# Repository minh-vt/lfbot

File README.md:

# LF-Bot

Du an robot tu hanh bam line va vuot chuong ngai vat cho cuoc thi F-Maze-Solving tai Dai hoc FPT. Repository gom firmware ESP32 (`firmware/`), PCB base 1 mat lam tai nha (`hardware/`) va tai lieu (`docs/`).

## Bat dau

Cai `just` va cac cong cu build theo [huong dan phat trien](AGENTS.md), sau do xem cac tac vu tai thu muc goc:

```sh
just --list
```

Cac lenh thuong dung: `just test` de kiem thu, `just build` de dich firmware ESP32. Danh sach tac vu duoc quan ly trong [justfile](justfile).

## Tai lieu

- [Kien truc](docs/ARCHITECTURE.md), [trang thai](docs/IMPLEMENTATION.md) va [viec con lai](docs/PLAN.md)
- [Quyet dinh kien truc](docs/decisions/README.md)
- [Quy tac dong gop va lam viec voi agent](AGENTS.md)
- [The le](docs/manual.md) va [hoi dap cuoc thi](docs/fqa.csv)
- [BOM phan cung](docs/HARDWARE_BOM.csv)
- [Phan cung module va huong dan dau day](hardware/README.md)

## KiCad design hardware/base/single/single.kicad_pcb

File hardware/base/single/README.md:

# BASE 1 mặt: làm tại nhà với cầu nối 0 Ω

Cùng linh kiện với [PCB base](../README.md) bản 0.7; mạch điện giống, trừ hai chân ESP32 đổi chỗ và J10 không có +5V (xem [Thiết kế lại cho 1 mặt](#thiết-kế-lại-cho-1-mặt)). Toàn bộ đường mạch nằm ở **mặt dưới**. Chỗ phải bắc qua đường khác thì dùng **điện trở 0 Ω dán ở mặt dưới** hoặc **dây nhảy ở mặt trên**. Chỉ ăn mòn một mặt, không phải căn hai phim, không có mối hàn nào ở mặt trên. Đây là board xe dùng để thi.

**Trạng thái: bản 0.7, file làm mạch đã xuất, chưa làm thử.**
- **DRC** theo luật làm tay trong [single.kicad_pro](single.kicad_pro) (dây 0,3 mm, khe hở 0,25 mm): 0 lỗi, 0 cảnh báo, 0 chân hở, khớp schematic.
- **[check_top.py](gen/check_top.py):** 0 mối hàn mặt trên.
- **`check_weird.py` của KiCadRoutingTools:** không có đầu dây treo, mối nối mỏng, đồng trùng hay via nổi. Còn 2 đoạn đồng thừa ngắn (0,2 và 0,4 mm) nằm trong đồng cùng net (vô hại).
- **Firmware:** `firmware/esp32/pins.hpp` theo board này (SDA = GPIO15, TOF_XSHUT = GPIO17).
- **Lưu ý khi tự kiểm:** `board_score.py` và `route_review.py` của KiCadRoutingTools báo nhiều net "hở" trên board này. Chúng không hiểu footprint cầu nối (hai pad cùng số, KiCad coi là nối với nhau). Đã kiểm: tắt cờ cầu nối thì KiCad cũng báo đúng các chỗ đó, bật lại thì 0. Với board này, DRC của KiCad là chuẩn.

## So với bản 2 lớp (`../fab`)

| | Bản 2 lớp | **1 mặt (bản này)** |
|---|---|---|
| Ăn mòn | xưởng làm, mạ lỗ | **1 mặt, tại nhà** |
| Qua đường khác | 36 via mạ lỗ | **3 điện trở 0 Ω + 2 dây nhảy** |
| Lỗ khoan | — | **153** |
| Mối hàn ở mặt trên | — | **0** |
| GND | đổ hai mặt | đổ mặt dưới |

Khác so với bản xưởng:
- D1 (SS14) nằm ở mặt dưới, dưới module buck: mặt dưới chỗ đó trống, module chỉ có chân xuyên qua. D1 thẳng hàng với chân 5V của ESP32 (U1.21) nên +5V là một đường thẳng; anode chéo 45° tới chân OUT+ của buck. VBAT_SW chạy dưới thân D1, giữa hai pad, nên không cần cầu nối ở đó.
- Chia áp đo pin xếp lại quanh chân ADC (U1.41): đầu VBAT_SENSE của R1 và R2 quay vào nhau hai bên chân đó, C2 (song song R2) nằm ngay trên R2, chân đối chân. VBAT_SENSE còn khoảng 9 mm đồng (trước 15 mm).
- J4 (chọn chân IR của thanh) dời lên dải trước, cạnh J3. J10 (I2C mở rộng) dời vào giữa mép phải, ngay trên bus.
- SDA và TOF_XSHUT đổi chân ESP32; J10 chân 1 để trống.

## Cầu nối

- **3 điện trở 0 Ω** dán ở mặt dưới, tên JP… trên `so_do_lap_mat_duoi.pdf`:
  - JP1 (1206): VBAT_SW qua MOT_L_A, gần DRV trái;
  - JP2 (0805): ENC_L_B qua ENC_L_A, gần giắc encoder trái;
  - JP3 (1206): GND qua +3V3, cạnh U1.1, nối mảnh GND quanh chân AD0 của IMU (J6.7).
  - Mua dư: vài cái 0805 và 1206.
- **2 dây nhảy ở mặt trên** (4 lỗ), tổng khoảng 11,5 mm, dài nhất 6,4 mm:
  - +3V3 qua ba đường bus, ngay dưới J10;
  - IMU_INT qua ba đường bus, dưới module ESP32.
  Dây đồng có vỏ bọc (hoặc dây trần nếu ngắn và không chạm gì), xỏ qua hai lỗ riêng, hàn ở mặt dưới.
- **2 lỗ dây nhảy IMU_INT nằm dưới bi cầu**, ở (4,5; −51,5) và (7,3; −55,4): giũa mối hàn mặt dưới cho phẳng.

## File để làm ([release/v0.7](release/v0.7/))

Mọi trang 1:1 có **vạch 100 mm**. In xong đo vạch bằng thước: lệch là máy in đã co giãn.

| File | Dùng làm gì |
|---|---|
| `phim/dong_mat_duoi.pdf` | Phim mặt dưới, đồng màu đen. Không lật gương: úp mặt in vào đồng |
| `phim/dong_mat_duoi_AM-BAN.pdf` | Cùng phim, dạng âm bản (đồng trong suốt) |
| `phim/chu_mat_tren_ui_lat_guong.pdf` | Chữ in mặt trên để ủi (tuỳ chọn) |
| `phim/*_4ban.pdf` | Ba phim trên, mỗi tờ A4 dọc 4 bản (2 × 2, khe 6 mm để cắt rời): in thử, chọn bản đẹp nhất hoặc giữ làm dự phòng. Có thêm vạch 100 mm dọc bên cạnh: đo cả hai chiều, vì máy in có thể co giãn mỗi chiều một khác |
| `so_do_day_nhay_mat_tren.pdf` | Vị trí 2 dây nhảy, nhìn từ trên. **Không phải phim** |
| `so_do_lap_mat_tren.pdf`, `so_do_lap_mat_duoi.pdf` | Sơ đồ lắp; mặt dưới vẽ như nhìn từ dưới lên, có các điện trở 0 Ω. In 1:1 rồi đặt devkit, DRV, gá motor, thanh IR, bi cầu, buck lên giấy để kiểm lỗ trước khi làm mạch |
| `khoan/single-PTH.drl`, `single-NPTH.drl`, `*-drl_map.pdf` | File khoan và bản đồ lỗ |
| `LF-Bot_base-1side_v0.7_gerber.zip` | Gửi xưởng (in mạch 1 lớp hoặc phay CNC). Trong zip có `GHI_CHU_DAT_XUONG.txt`: 1 lớp đồng ở **mặt dưới**, mọi lỗ không mạ, kích thước, khe oval, luật nhỏ nhất. Đặt hàng chọn 1 lớp, FR-4 1,6 mm, và chép ý chính của ghi chú vào ô ghi chú đơn hàng |
| `LF-Bot_base-1side_v0.7.step` | Mô hình 3D để ghép trong CAD cơ khí |

**Chọn phim theo loại keo** như bản 2 mặt: phim khô hoặc keo UV loại âm dùng `AM-BAN`; tấm phủ sẵn cảm quang dương hoặc ủi mực laser dùng bản thường.

## Các bước

1. **Mặt trên không giữ đồng:** dùng phíp 1 mặt, hoặc với phíp 2 mặt thì không phủ keo mặt trên để FeCl₃ ăn hết đồng mặt đó. Nếu còn sót đồng ở mặt trên, mọi chân linh kiện xuyên lỗ sẽ chập vào nhau.
2. **Tạo mạch mặt dưới:** in phim, phủ keo, chiếu UV, rửa hiện hình, ăn mòn, tẩy keo.
3. **Ủi chữ mặt trên** (tuỳ chọn).
4. **Khoan** theo chấm tâm (153 lỗ):

   | Mũi | Lỗ | Số lỗ |
   |---|---|---|
   | 0,7 mm | lỗ dây nhảy (4); chân giắc JST ZH 0,73 mm (12) | 16 |
   | 0,8 mm | chân C1 | 2 |
   | 1,0 mm | header, socket, IMU (93); chân F1 (2) | 95 |
   | 1,2 mm | nút (8); pad dây công tắc (2); pad dây DRV (8) | 18 |
   | 1,3 mm | chân buck | 8 |
   | 1,8 mm | pad dây pin | 2 |
   | 2,2 mm | lỗ gá motor (4); 2 khe bi cầu | 4 + 2 khe |
   | 3,2 mm | lỗ khay pin (4); 2 khe thanh IR | 4 + 2 khe |
5. **Linh kiện dán ở mặt dưới:**
   - 18 điện trở và tụ;
   - D1 dưới chỗ module buck, vạch quay về phía ESP32 (+5V). Hàn trước khi lắp buck; đường VBAT_SW chạy giữa hai pad (khe 0,45 mm mỗi bên), không để thiếc tràn;
   - 3 điện trở 0 Ω, đặt theo tên JP trên sơ đồ lắp mặt dưới.
   - 16 điện trở chia áp IR nằm thành 8 cột sau J3, 10k ở hàng gần J3, 47k ở hàng sau. Nhìn từ mặt dưới, cột D1 ở bên phải.
6. **2 dây nhảy ở mặt trên** theo `so_do_day_nhay_mat_tren.pdf`, hàn ở mặt dưới. Làm trước các linh kiện cao để dễ luồn dây.
7. **Linh kiện xuyên lỗ:** tất cả hàn ở mặt dưới như mạch 1 mặt bình thường, kể cả C1 (lắp sát board được).
8. **Kiểm trước khi cắm module:**
   - đo thông GND giữa J1, pad GND của U2/U3 và chân GND của ESP32;
   - đo thông hai đầu mỗi dây nhảy và mỗi điện trở 0 Ω;
   - đo không chập VBAT_SW–GND, +5V–GND, +3V3–GND;
   - cấp nguồn khi chưa cắm ESP32, chỉnh buck lên khoảng 5,2–5,3 V.

Cách đấu module: [wiring.md](../../wiring.md). Danh sách mua linh kiện chung: [../fab/release/v0.7](../fab/release/v0.7/README.md); thêm các điện trở 0 Ω ở trên.

## Sinh lại

Đọc vị trí từ `../fab/base.kicad_pcb`:

- [gen/make_single.sh](gen/make_single.sh), khoảng 3 phút:
  - gỡ đồng;
  - [gen/prepare.py](gen/prepare.py): chuyển linh kiện dán và D1 xuống dưới, dời J4, J10 và D1, gán net theo `VARIANT_PINS` trong `../gen/design.py`, đánh dấu các chân nối sẵn bên trong linh kiện, cấm đồng mặt trên ở mọi pad, cấm dây nhảy dưới thân linh kiện áp sát board;
  - [gen/guide.py](gen/guide.py): vẽ sẵn bus I2C/ToF và IR_CTRL, khoá lại;
  - đổ GND mặt dưới;
  - route phần còn lại bằng KiCadRoutingTools, mặt trên đắt gấp 30 lần để chỉ dùng khi mặt dưới hết đường. Thứ tự: nguồn, kênh IR, phần còn lại. GND không đưa vào lượt nào, vì bước tự nối GND của KiCadRoutingTools sẽ kéo đồng GND lên mặt trên;
  - làm gọn (`../gen/tidy_tracks.py`), đưa đầu dây vào tâm lỗ (`../gen/center_vias.py`);
  - [gen/jumpers.py](gen/jumpers.py), mỗi bước chỉ giữ khi DRC không báo lỗi mới: đổi dây nhảy ngắn thành 0 Ω 0805 hoặc 1206, trượt dọc dây cho đường bên dưới nằm giữa hai pad; gộp chuỗi "dây – đoạn dưới – dây" thành một dây; thay 0 Ω không bắc qua gì bằng đoạn đồng. Chạy cả hai thứ tự (0 Ω trước, gộp trước) rồi giữ bản ít lỗ hơn;
  - [gen/gnd_bridges.py](gen/gnd_bridges.py): mảnh GND nào bị đường mạch bao kín thì nối sang mảnh gần nhất bằng 0 Ω (hoặc dây nhảy nếu xa), giữ khi DRC cho phép;
  - [gen/prune.py](gen/prune.py): bỏ đồng không mang dòng: đoạn mà `check_weird` của KiCadRoutingTools coi là bỏ được, và đoạn nối thẳng hai chân đã nối sẵn trong linh kiện (router không biết các chân đó nối trong, KiCad thì biết). Mỗi đoạn chỉ bỏ khi DRC không báo lỗi hay chân hở mới;
  - sắp nhãn, chạy DRC.
- [gen/export.sh](gen/export.sh): xuất `release/<bản>`.
- Schematic `single.kicad_sch` do `../gen/run_all.sh` sinh cùng bản 2 lớp, với các chân đổi trong `VARIANT_PINS`. Footprint `Jumper_0R_0805` và `Jumper_0R_1206` do `../gen/gen_fp.py` sinh.

## Thiết kế lại cho 1 mặt

Bản trước (route tự động hoàn toàn) cần 24 cầu nối, 18 lỗ. Ba điều về hình học của board quyết định số đó:

- **Dải chia áp chỉ có một khe trống.** 8 cột điện trở có 9 khe, mỗi khe chỉ lọt một đường 0,3 mm. 8 đường ADC đã cần 8 khe, chỉ còn khe x = 1,27 mm (giữa cột IR4 và IR5, thẳng hàng với khe giữa chân 6 và 7 của J3).
- **GND của các điện trở 47k chỉ vào được từ phía module.** Mỗi pad GND kẹp giữa hai đường ADC, nối được qua khe giữa các chân hàng trước của ESP32. Dải ngay sau hàng chân đó phải để cho GND.
- **Thứ tự chân của ToF (SDA, SCL, XSHUT), IMU và J10 cố định.**

Thiết kế lại theo đó:

- **Đổi SDA và TOF_XSHUT trên ESP32** (SDA sang U1.8 = GPIO15, XSHUT sang U1.10 = GPIO17). Ba đường bus khi chui xuống dưới module thì nằm cạnh nhau đúng thứ tự ToF cần.
- **Bus đi vòng, không bắt chéo gì:** từ U1.8–U1.10 xuống dưới module, chạy dưới thân IMU (cách dải GND sau hàng chân), rẽ lên mép phải, đi xuyên qua chân SDA/SCL của IMU (J6.4, J6.3) rồi của J10 (J10.4, J10.5; XSHUT đi khe bên cạnh), dọc mép trước rồi vào ToF đúng thứ tự chân. IMU giữ nguyên chỗ: chân SDA/SCL của nó vốn nằm đúng trên đường đi lên.
- **IR_CTRL lấy khe trống duy nhất** của dải chia áp để lên J4, nay đặt ở dải trước.
- **Bỏ +5V khỏi J10:** nhánh này trước đi vòng gần hết board.
- **Cầu nối miễn phí:** các chân mà linh kiện đã nối sẵn bên trong được khai báo là nối với nhau, nên đường mạch được dùng chúng để đi qua: hai chân cùng phía của mỗi nút 6 mm, các chân GND và hai chân 3V3 của DevKit ESP32, hai chân của mỗi cực MP1584 (cùng xuyên qua một pad của module), GND vào và ra của MP1584.
- **D1 dưới module buck**, thẳng hàng chân 5V của ESP32: +5V không còn vòng ra ngoài module rồi bắt chéo VBAT_SW.

Kết quả: 3 điện trở 0 Ω + 2 dây nhảy (4 lỗ). Mỗi cầu còn lại có lý do riêng: IMU_INT và +3V3 phải vượt ba đường bus để tới IMU và phía sau board; hai cầu ở phía sau (VBAT_SW qua motor trái, encoder trái) có từ bản đầu; JP3 nối mảnh GND quanh chân AD0 của IMU.

## Đã thử giảm cầu nối

Mục tiêu: ít cầu nối nhất mà vẫn nối đủ mọi net. Mỗi cách đều xây lại toàn bộ board rồi đếm:

| Cách | Kết quả |
|---|---|
| Cho đường mạch chạy dưới thân linh kiện có sẵn (D1, điện trở, tụ) thay cho cầu nối | KiCadRoutingTools vốn được phép làm vậy (bản xưởng có đường chạy dưới C2, R21, R22). Ở chỗ cũ của D1 nó không thấy lợi; khi D1 vào dưới module buck thì VBAT_SW chạy dưới thân D1 và bỏ được một dây nhảy |
| Thay điện trở 0 Ω không bắc qua gì bằng dây đồng thẳng | Bớt được 2 cái (17 → 15) |
| Trượt 0 Ω dọc dây nhảy: khe 0,8 mm của 0805 chỉ vừa một đường 0,3 mm với khe hở 0,25 mm mỗi bên, mà router không đặt đường vào giữa | Thêm được 0 Ω ở những chỗ trước bị chạm pad |
| Gộp chuỗi "dây – đoạn dưới – dây": router xuống mặt dưới một đoạn ngắn chỉ để một dây khác đi qua, nhưng dây có vỏ được bắt chéo nhau | 5 chuỗi gộp được. Cùng hai bước trên: 13 → 9 dây nhảy, 26 → 18 lỗ |
| Phạt via nặng hơn trong KiCadRoutingTools (`--via-cost` 1000–3000, mặt trên đắt gấp 100 lần) | Tệ hơn: các đường đi vòng xa chặn net route sau, còn 6–13 đường chưa nối, có dây dài 112 mm |
| Bỏ +5V khỏi J10 | Một lần route còn 4 đường chưa nối: router quá nhạy với thay đổi nhỏ để kết luận |
| Bỏ +5V khỏi J10 và vẽ tay trước bus mà không đổi chân: SCL qua khe giữa dải chia áp, SDA/SCL dưới module ESP32 sang IMU và J10, IR_CTRL dưới module sang J4 (8 cách phối hợp) | Bản tốt nhất có 23 cầu nối nhưng vẫn còn mảnh GND rời; nối các mảnh đó thì thành khoảng 25 |
| Thiết kế lại ở trên (đổi chân SDA/XSHUT, dời J4/J10, bus vẽ tay), D1 còn ở chỗ cũ cạnh buck | 6 cầu nối, 6 lỗ |
| Như trên, D1 dưới module buck | **5 cầu nối, 4 lỗ**: đang dùng |
| Vẽ tay thêm +3V3 (một dây nhảy phía bắc J10 xuống IMU) | 11 cầu nối: router đổi cách đưa +3V3 ra phía sau và bắt chéo encoder; không dùng |
| Hoán đổi chân GPIO bằng target swap của KiCadRoutingTools | Không bớt được cầu nối nào, lại đổi bảng chân; không dùng |
| Đặt lại J10, J4, J9, nút, D1, R1/R2/C2 bằng placer của KiCadRoutingTools (12 phương án, 6 phương án tốt nhất được route đầy đủ) | Các phương án ít cầu nối hơn đều còn 3–16 đường chưa nối, mà mỗi đường hở lại cần thêm cầu nối; không phương án nào hơn |

Router đặt từng net một, theo đường ngắn nhất lúc đó, nên không tìm cách sắp xếp ít chỗ bắt chéo cho cả board. Vì vậy bus được vẽ tay, router chỉ làm phần còn lại.

## Giới hạn

- Chưa làm thử.
- Không có lớp phủ xanh: hàn cẩn thận chỗ đường mạch chạy dưới điện trở 0 Ω (khe 0,25 mm).
- Pad giắc JST ZH chỉ có vành 0,15 mm, như hai bản kia.
- Mặt dưới còn 1 góc 90°, 2 đoạn lệch góc và 7 đoạn ngắn dưới 0,2 mm (đo bằng [geometry_report.py](../gen/geometry_report.py)), không ảnh hưởng điện. Chạy thêm `tidy_tracks.py` ở cuối không gọn hơn.

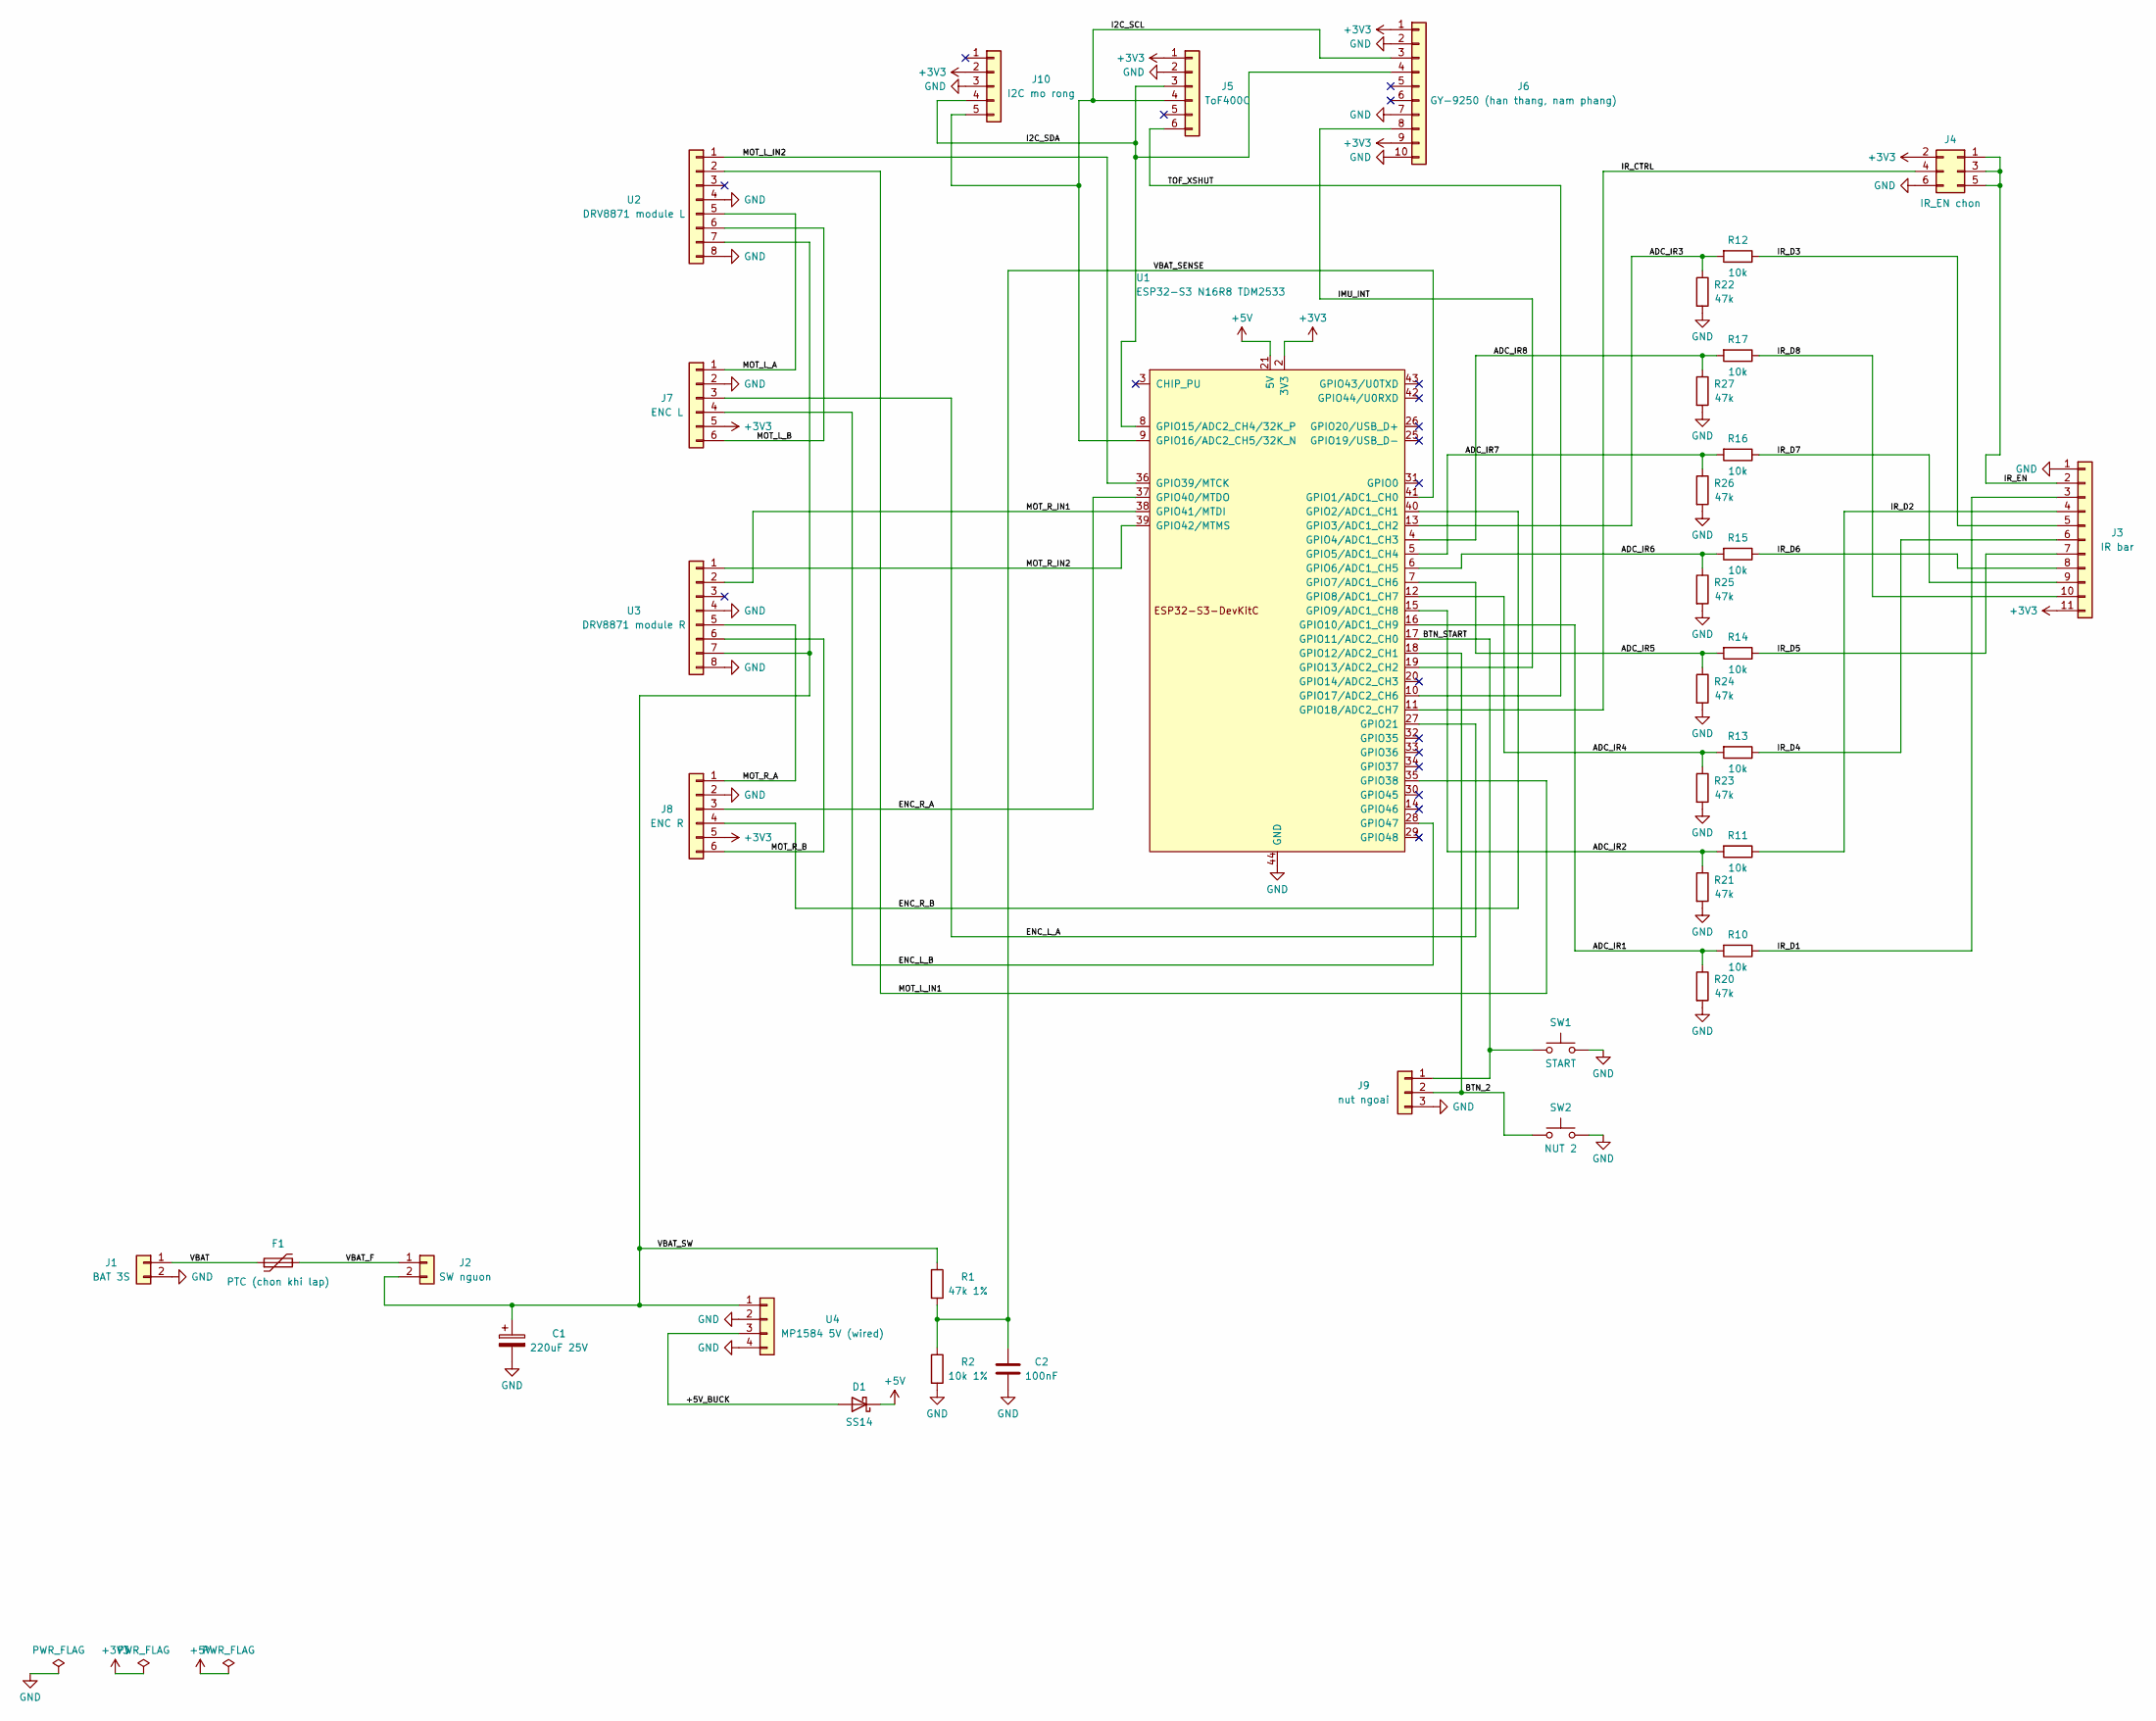
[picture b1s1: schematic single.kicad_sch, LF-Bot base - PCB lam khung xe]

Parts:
C1: 220uF 25V; CP_Radial_D6.3mm_P2.50mm
C2: 100nF; C_0805_2012Metric_Pad1.18x1.45mm_HandSolder
D1: SS14; D_SMA_Handsoldering
F1: PTC (chon khi lap); Fuse_Bourns_MF-RG500
J1: BAT 3S; SolderWire-1sqmm_1x02_P5.4mm_D1.4mm_OD2.7mm
J2: SW nguon; SolderWire-0.5sqmm_1x02_P4.8mm_D0.9mm_OD2.3mm
J3: IR bar; PinHeader_1x11_P2.54mm_Vertical
J4: IR_EN chon; PinHeader_2x03_P2.54mm_Vertical
J5: ToF400C; PinSocket_1x06_P2.54mm_Vertical
J6: GY-9250 (han thang, nam phang); GY9250_Flat
J7: ENC L; JST_ZH_B6B-ZR_1x06_P1.50mm_Vertical
J8: ENC R; JST_ZH_B6B-ZR_1x06_P1.50mm_Vertical
J9: nut ngoai; PinHeader_1x03_P2.54mm_Vertical
J10: I2C mo rong; PinHeader_1x05_P2.54mm_Vertical
R1: 47k 1%; R_0805_2012Metric_Pad1.20x1.40mm_HandSolder
R2: 10k 1%; R_0805_2012Metric_Pad1.20x1.40mm_HandSolder
R10, R11, R12, R13, R14, R15, R16, R17: 10k; R_0805_2012Metric_Pad1.20x1.40mm_HandSolder
R20, R21, R22, R23, R24, R25, R26, R27: 47k; R_0805_2012Metric_Pad1.20x1.40mm_HandSolder
SW1: START; SW_PUSH_6mm
SW2: NUT 2; SW_PUSH_6mm
U1: ESP32-S3 N16R8 TDM2533; ESP32-S3-DevKitC_TDM2533
U2: DRV8871 module L; DRV8871_Module
U3: DRV8871 module R; DRV8871_Module
U4: MP1584 5V (wired); MP1584_Wired

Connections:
+3V3: J3.11, J4.2, J5.1, J6.1, J6.9, J7.5, J8.5, J10.2, U1.1 (3V3), U1.2 (3V3)
+5V: D1.1 (K), U1.21 (5V)
/+5V_BUCK: D1.2 (A), U4.3
/ADC_IR1: R10.2, R20.1, U1.16 (GPIO10/ADC1_CH9)
/ADC_IR2: R11.2, R21.1, U1.15 (GPIO9/ADC1_CH8)
/ADC_IR3: R12.2, R22.1, U1.13 (GPIO3/ADC1_CH2)
/ADC_IR4: R13.2, R23.1, U1.12 (GPIO8/ADC1_CH7)
/ADC_IR5: R14.2, R24.1, U1.7 (GPIO7/ADC1_CH6)
/ADC_IR6: R15.2, R25.1, U1.6 (GPIO6/ADC1_CH5)
/ADC_IR7: R16.2, R26.1, U1.5 (GPIO5/ADC1_CH4)
/ADC_IR8: R17.2, R27.1, U1.4 (GPIO4/ADC1_CH3)
/BTN_2: J9.2, SW2.1, U1.18 (GPIO12/ADC2_CH1)
/BTN_START: J9.1, SW1.1, U1.17 (GPIO11/ADC2_CH0)
/ENC_L_A: J7.3, U1.27 (GPIO21)
/ENC_L_B: J7.4, U1.28 (GPIO47); also elsewhere on the board
/ENC_R_A: J8.3, U1.37 (GPIO40/MTDO)
/ENC_R_B: J8.4, U1.40 (GPIO2/ADC1_CH1)
/I2C_SCL: J5.4, J6.3, J10.5, U1.9 (GPIO16/ADC2_CH5/32K_N)
/I2C_SDA: J5.3, J6.4, J10.4, U1.8 (GPIO15/ADC2_CH4/32K_P)
/IMU_INT: J6.8, U1.19 (GPIO13/ADC2_CH2)
/IR_CTRL: J4.4, U1.11 (GPIO18/ADC2_CH7)
/IR_D1: J3.3, R10.1
/IR_D2: J3.4, R11.1
/IR_D3: J3.5, R12.1
/IR_D4: J3.6, R13.1
/IR_D5: J3.7, R14.1
/IR_D6: J3.8, R15.1
/IR_D7: J3.9, R16.1
/IR_D8: J3.10, R17.1
/IR_EN: J3.2, J4.1, J4.3, J4.5
/MOT_L_A: J7.1, U2.5
/MOT_L_B: J7.6, U2.6
/MOT_L_IN1: U1.35 (GPIO38), U2.2
/MOT_L_IN2: U1.36 (GPIO39/MTCK), U2.1
/MOT_R_A: J8.1, U3.5
/MOT_R_B: J8.6, U3.6
/MOT_R_IN1: U1.38 (GPIO41/MTDI), U3.2
/MOT_R_IN2: U1.39 (GPIO42/MTMS), U3.1
/TOF_XSHUT: J5.6, U1.10 (GPIO17/ADC2_CH6)
/VBAT: F1.1, J1.1
/VBAT_F: F1.2, J2.1
/VBAT_SENSE: C2.1, R1.2, R2.1, U1.41 (GPIO1/ADC1_CH0)
/VBAT_SW: C1.1, J2.2, R1.1, U2.7, U3.7, U4.1; also elsewhere on the board
GND: C1.2, C2.2, J1.2, J3.1, J4.6, J5.2, J6.2, J6.7, J6.10, J7.2, J8.2, J9.3, J10.3, R2.2, R20.2, R21.2, R22.2, R23.2, R24.2, R25.2, R26.2, R27.2, SW1.2, SW2.2, U1.22 (GND), U1.23 (GND), U1.24 (GND), U1.44 (GND), U2.4, U2.8, U3.4, U3.8, U4.2, U4.4; also elsewhere on the board

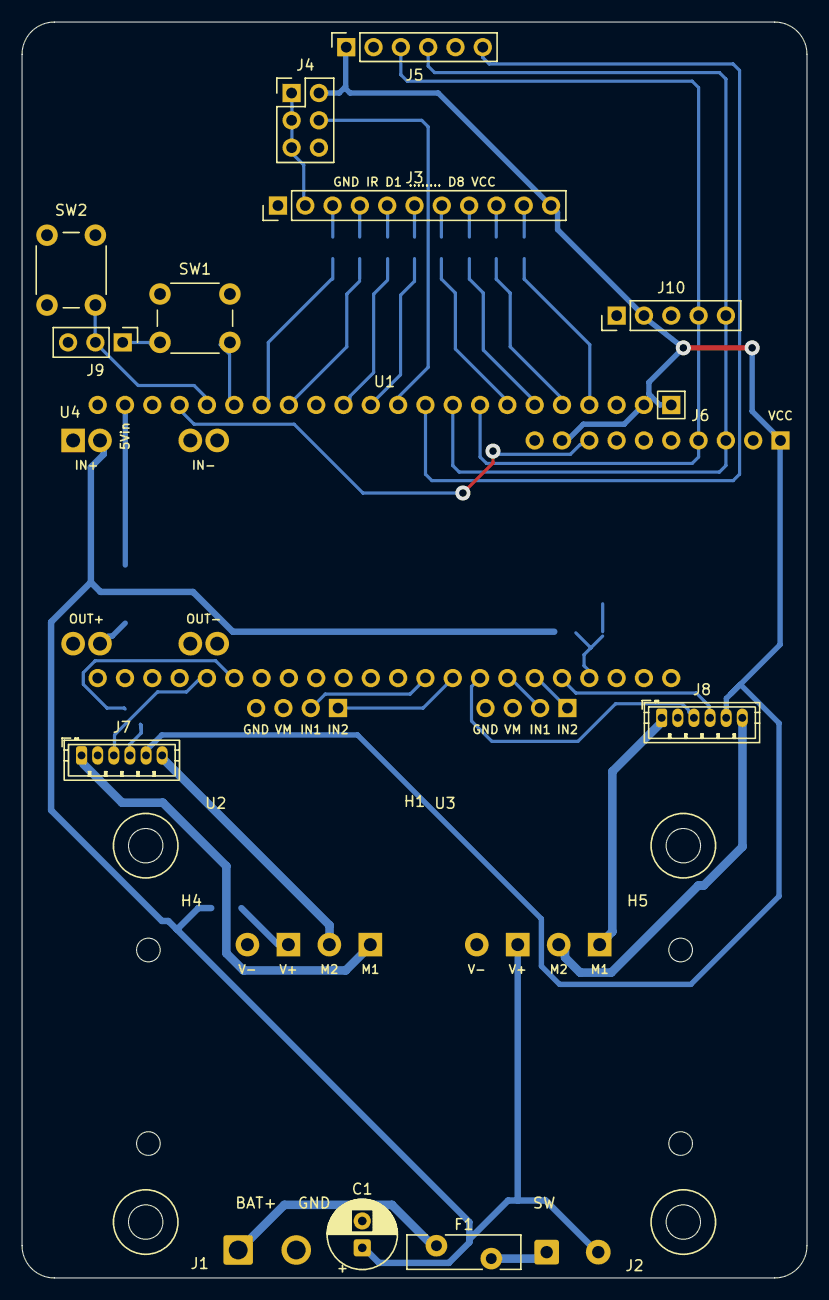
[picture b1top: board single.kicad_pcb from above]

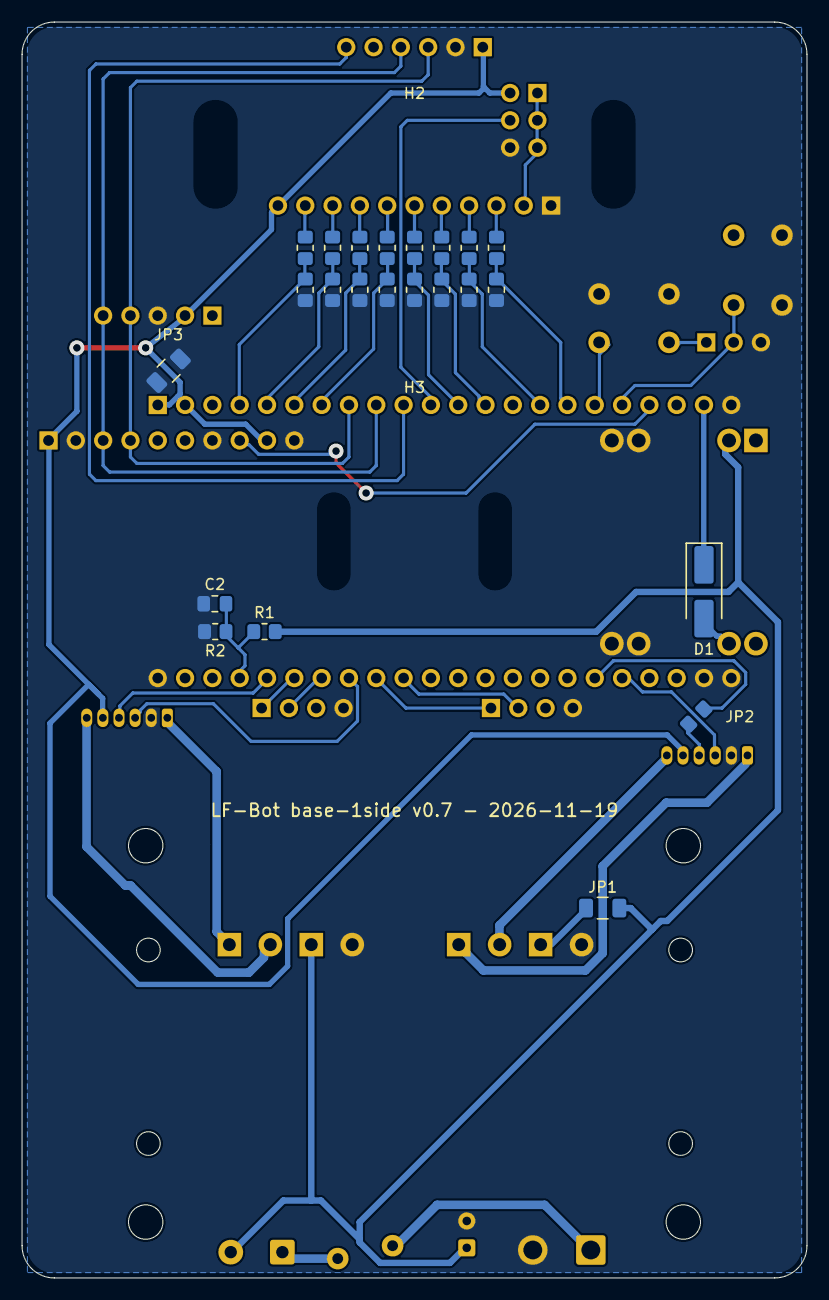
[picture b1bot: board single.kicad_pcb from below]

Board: 2 copper layers, 73.0 x 116.8 mm, 46 parts (25 on the bottom side), 44 nets.

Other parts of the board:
H1: Stack_Mount_50x35
H2: IR_Bar_Mount_37mm
H3: Caster_Mount_15mm
H4, H5: N20_Bracket_Mount
JP1, JP3: 0R 1206; Jumper_0R_1206
JP2: 0R 0805; Jumper_0R_0805

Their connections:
/ENC_L_B: JP2.1; also elsewhere on the board
/VBAT_SW: JP1.1; also elsewhere on the board
GND: JP3.1; also elsewhere on the board

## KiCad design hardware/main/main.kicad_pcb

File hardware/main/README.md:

# MAIN LF-Bot — đã dừng

> **Thiết kế PCB đã dừng theo [ADR-019](../../docs/decisions/ADR-019-module-based-hardware.md).** Dùng [pin map module](../wiring.md) và [BOM hiện hành](../../docs/HARDWARE_BOM.csv); không gia công, route tiếp hoặc đấu dây theo board này.

Board mang DevKit ESP32-S3 và hai IC A4950 cũ. Source KiCad vẫn mở được bằng KiCad 10 qua [main.kicad_pro](main.kicad_pro); [schematic](main.kicad_sch) và [PCB](main.kicad_pcb) là bản lưu lịch sử: hai mặt linh kiện, 14 SMD tín hiệu ở B.Cu, chưa route xong, chưa kiểm chứng Z/lắp ráp/nhiệt.

Tài liệu placement/routing/BOM của board đã được archive và bỏ khỏi cây làm việc. Lý do dừng PCB nằm ở [ADR-019](../../docs/decisions/ADR-019-module-based-hardware.md).

Giữ `Main.pretty/`, `Main.kicad_sym`, library table, [cơ khí](mechanical/) và [datasheet motor](datasheets/GA12-N20.pdf) để phục hồi. `Bracket.step` vẫn là nguồn gá motor được chủ dự án xác nhận. Không gửi Gerber cũ đi in.

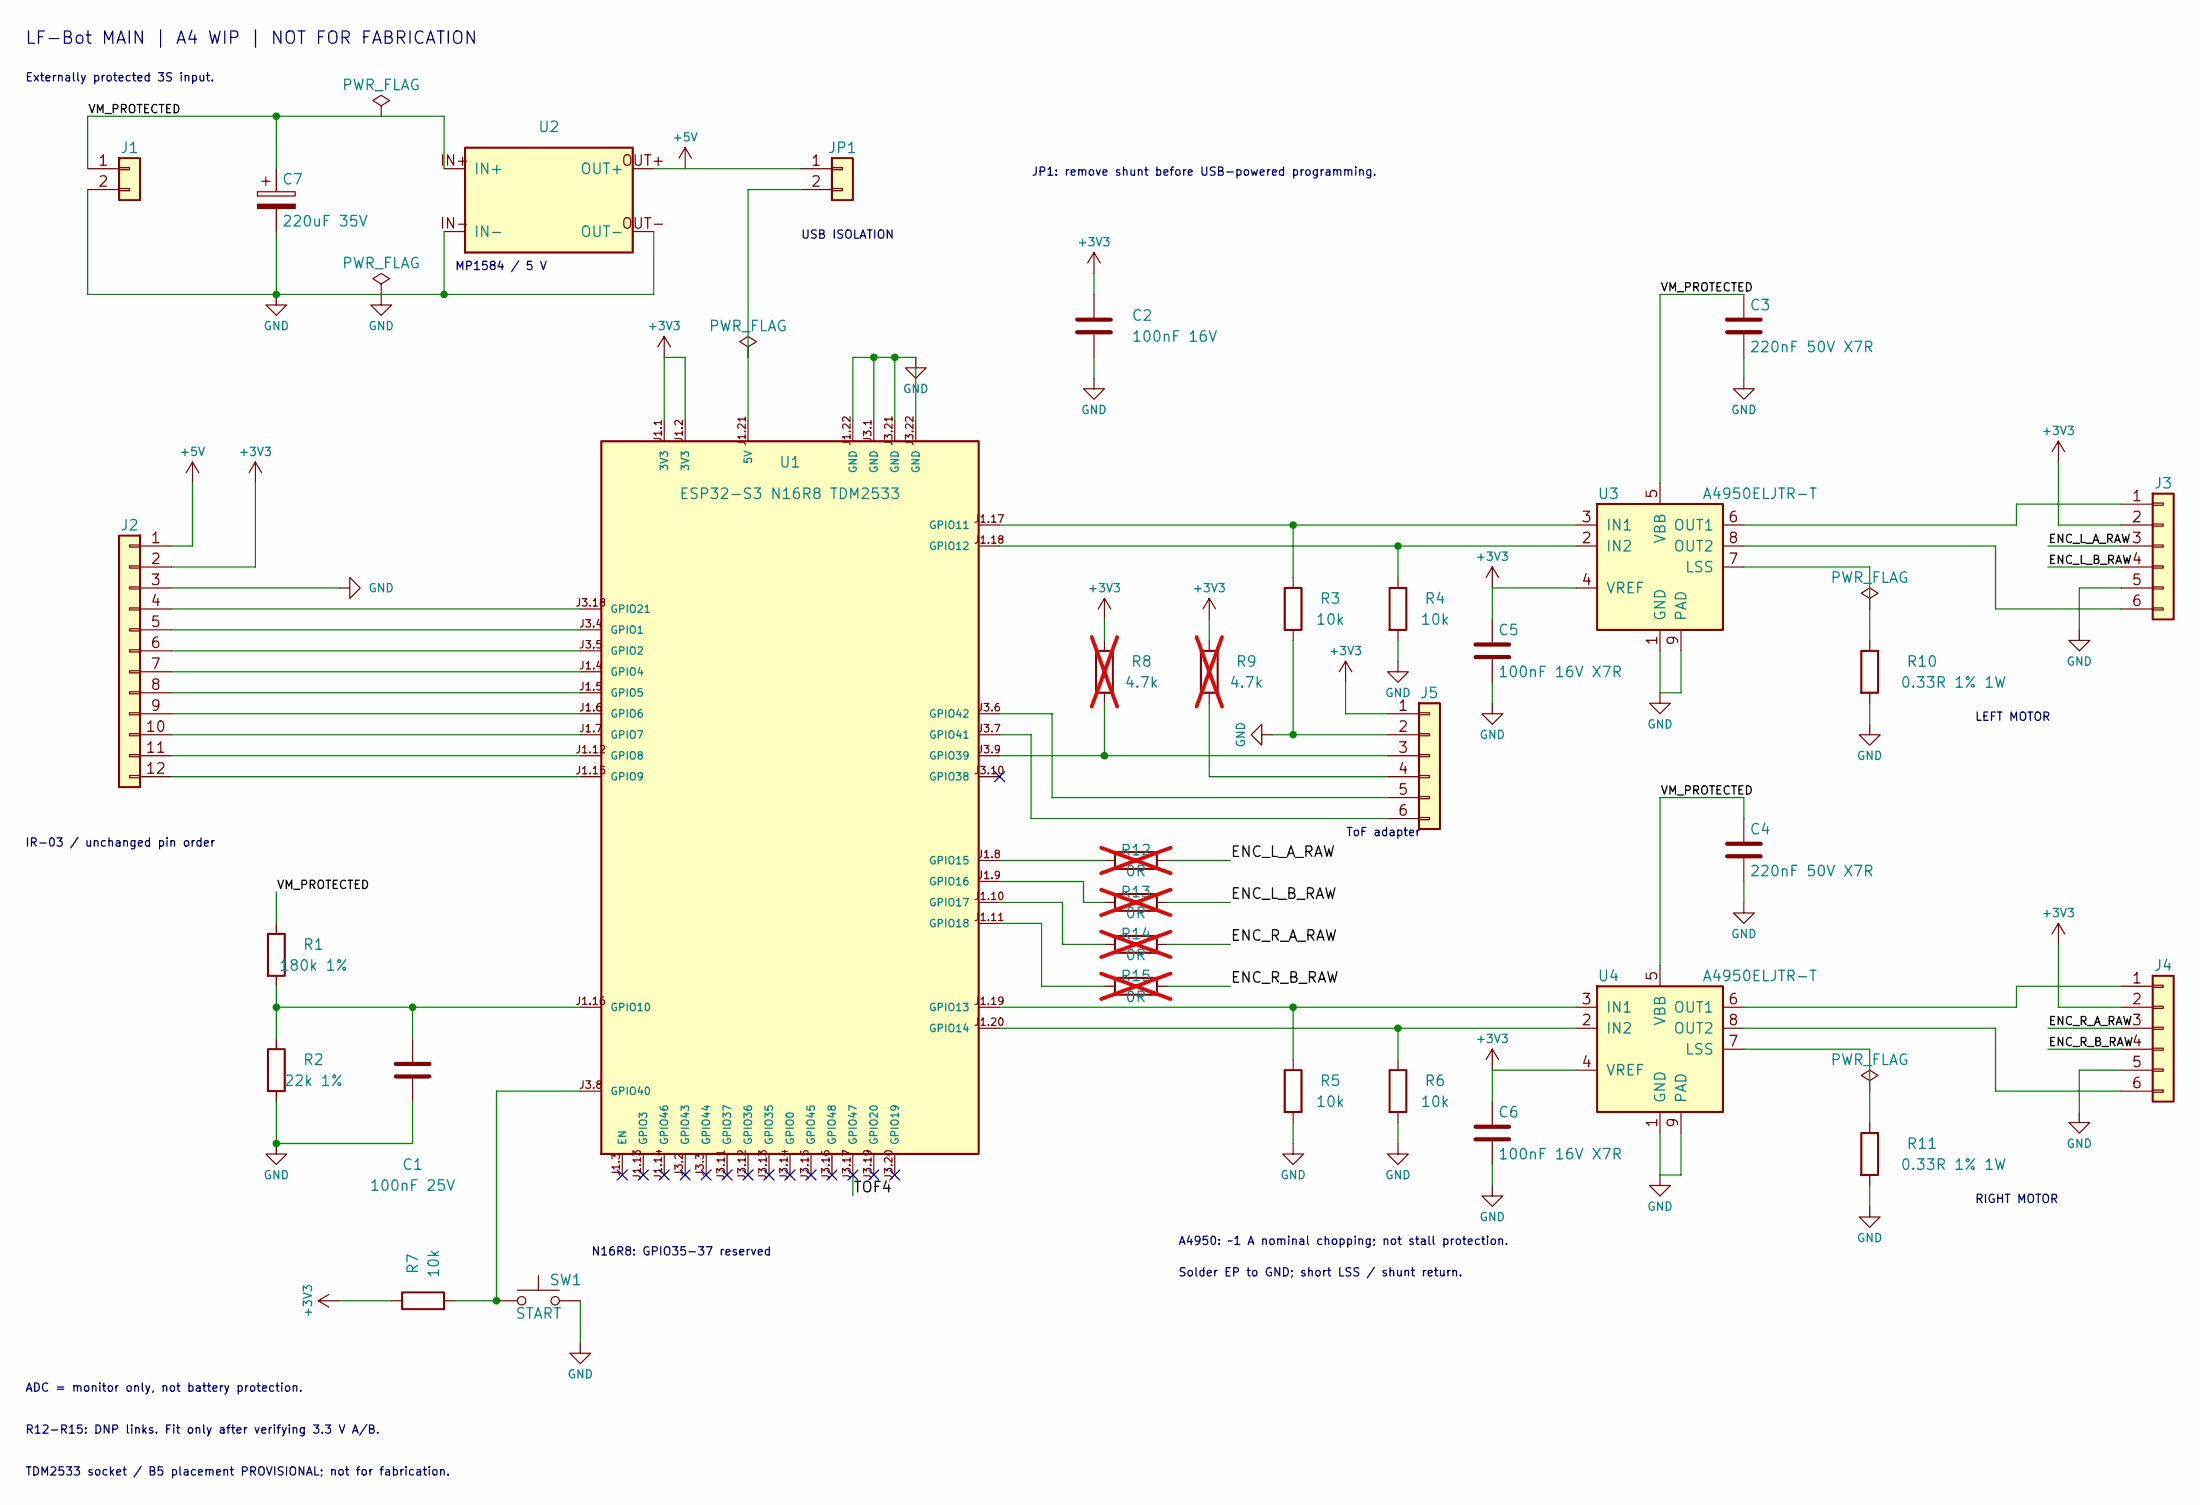
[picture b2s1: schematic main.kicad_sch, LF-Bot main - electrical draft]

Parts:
C1: 100nF 25V; C_0805_2012Metric
C2: 100nF 16V; C_0805_2012Metric
C3, C4: 220nF 50V X7R; C_0805_2012Metric
C5, C6: 100nF 16V X7R; C_0805_2012Metric
C7: 220uF 35V; CP_Radial_D8.0mm_P3.50mm; MPN 35ZLQ220MEFC8X11.5
J1: 3S PROTECTED INPUT / WIRED; SolderWire-0.5sqmm_1x02_P4.8mm_D0.9mm_OD2.3mm
J2: IR03 - SAME PINOUT AS IR BOARD; PinHeader_1x12_P2.54mm_Vertical
J3: LEFT MOTOR / XH 2.50; JST_XH_B6B-XH-A_1x06_P2.50mm_Vertical; MPN B6B-XH-A(LF)(SN)
J4: RIGHT MOTOR / XH 2.50; JST_XH_B6B-XH-A_1x06_P2.50mm_Vertical; MPN B6B-XH-A(LF)(SN)
J5: TOF400C / XH 2.50 ADAPTER; JST_XH_B6B-XH-A_1x06_P2.50mm_Vertical; MPN B6B-XH-A(LF)(SN)
JP1: REMOVE BEFORE USB POWER; PinHeader_1x02_P2.54mm_Vertical
R1: 180k 1%; R_0805_2012Metric
R2: 22k 1%; R_0805_2012Metric
R3, R4, R5, R6, R7: 10k; R_0805_2012Metric
R8, R9: 4.7k; R_0805_2012Metric; not fitted
R10, R11: 0.33R 1% 1W; R_2512_6332Metric
R12, R13, R14, R15: 0R; R_0805_2012Metric; MPN RC0805JR-070RL; not fitted
SW1: START; SW_PUSH_6mm_H5mm
U1: ESP32-S3 N16R8 TDM2533; ESP32-S3_DevKitC-1_Reference_Sockets; MPN TDM2533
U2: MP1584 FIXED 5V / WIRED; MP1584_Wire_Interface; MPN MP1584 fixed 5V module
U3, U4: A4950ELJTR-T; SOIC-8-1EP_3.9x4.9mm_P1.27mm_EP2.41x3.3mm; MPN A4950ELJTR-T

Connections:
+3V3: C2.1, C5.1, C6.1, J2.2, J3.2, J4.2, J5.1, R7.1, R8.1, R9.1, U1.J1.1 (3V3), U1.J1.2 (3V3), U3.4 (VREF), U4.4 (VREF)
+5V: J2.1, JP1.1, U2.OUT+
/ENC_L_A_RAW: J3.3, R12.2
/ENC_L_B_RAW: J3.4, R13.2
/ENC_R_A_RAW: J4.3, R14.2
/ENC_R_B_RAW: J4.4, R15.2
/TOF4: U1.J3.17 (GPIO47)
/VM_PROTECTED: C3.1, C4.1, C7.1, J1.1, R1.1, U2.IN+, U3.5 (VBB), U4.5 (VBB)
GND: C1.2, C2.2, C3.2, C4.2, C5.2, C6.2, C7.2, J1.2, J2.3, J3.5, J4.5, J5.2, R2.2, R3.2, R4.2, R5.2, R6.2, R10.2, R11.2, SW1.2, U1.J1.22 (GND), U1.J3.1 (GND), U1.J3.21 (GND), U1.J3.22 (GND), U2.IN-, U2.OUT-, U3.1 (GND), U3.9 (PAD), U4.1 (GND), U4.9 (PAD)
unnamed: J2.4, U1.J3.18 (GPIO21)
unnamed: J2.5, U1.J3.4 (GPIO1)
unnamed: J2.6, U1.J3.5 (GPIO2)
unnamed: J2.7, U1.J1.4 (GPIO4)
unnamed: J2.8, U1.J1.5 (GPIO5)
unnamed: J2.9, U1.J1.6 (GPIO6)
unnamed: J2.10, U1.J1.7 (GPIO7)
unnamed: J2.11, U1.J1.12 (GPIO8)
unnamed: J2.12, U1.J1.15 (GPIO9)
unnamed: J3.1, U3.6 (OUT1)
unnamed: J3.6, U3.8 (OUT2)
unnamed: J4.1, U4.6 (OUT1)
unnamed: J4.6, U4.8 (OUT2)
unnamed: J5.3, R8.2, U1.J3.9 (GPIO39)
unnamed: J5.4, R9.2
unnamed: J5.5, U1.J3.6 (GPIO42)
unnamed: J5.6, U1.J3.7 (GPIO41)
unnamed: JP1.2, U1.J1.21 (5V)
unnamed: C1.1, R1.2, R2.1, U1.J1.16 (GPIO10)
unnamed: R3.1, U1.J1.17 (GPIO11), U3.3 (IN1)
unnamed: R4.1, U1.J1.18 (GPIO12), U3.2 (IN2)
unnamed: R5.1, U1.J1.19 (GPIO13), U4.3 (IN1)
unnamed: R6.1, U1.J1.20 (GPIO14), U4.2 (IN2)
unnamed: R12.1, U1.J1.8 (GPIO15)
unnamed: R13.1, U1.J1.9 (GPIO16)
unnamed: R14.1, U1.J1.10 (GPIO17)
unnamed: R15.1, U1.J1.11 (GPIO18)
unnamed: R7.2, SW1.1, U1.J3.8 (GPIO40)
unnamed: R10.1, U3.7 (LSS)
unnamed: R11.1, U4.7 (LSS)

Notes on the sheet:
Externally protected 3S input.
USB ISOLATION
N16R8: GPIO35-37 reserved
LF-Bot MAIN | A4 WIP | NOT FOR FABRICATION
ADC = monitor only, not battery protection.
R12-R15: DNP links. Fit only after verifying 3.3 V A/B.
JP1: remove shunt before USB-powered programming.
ToF adapter
Solder EP to GND; short LSS / shunt return.
IR-03 / unchanged pin order
A4950: ~1 A nominal chopping; not stall protection.
MP1584 / 5 V
LEFT MOTOR
RIGHT MOTOR
TDM2533 socket / B5 placement PROVISIONAL; not for fabrication.

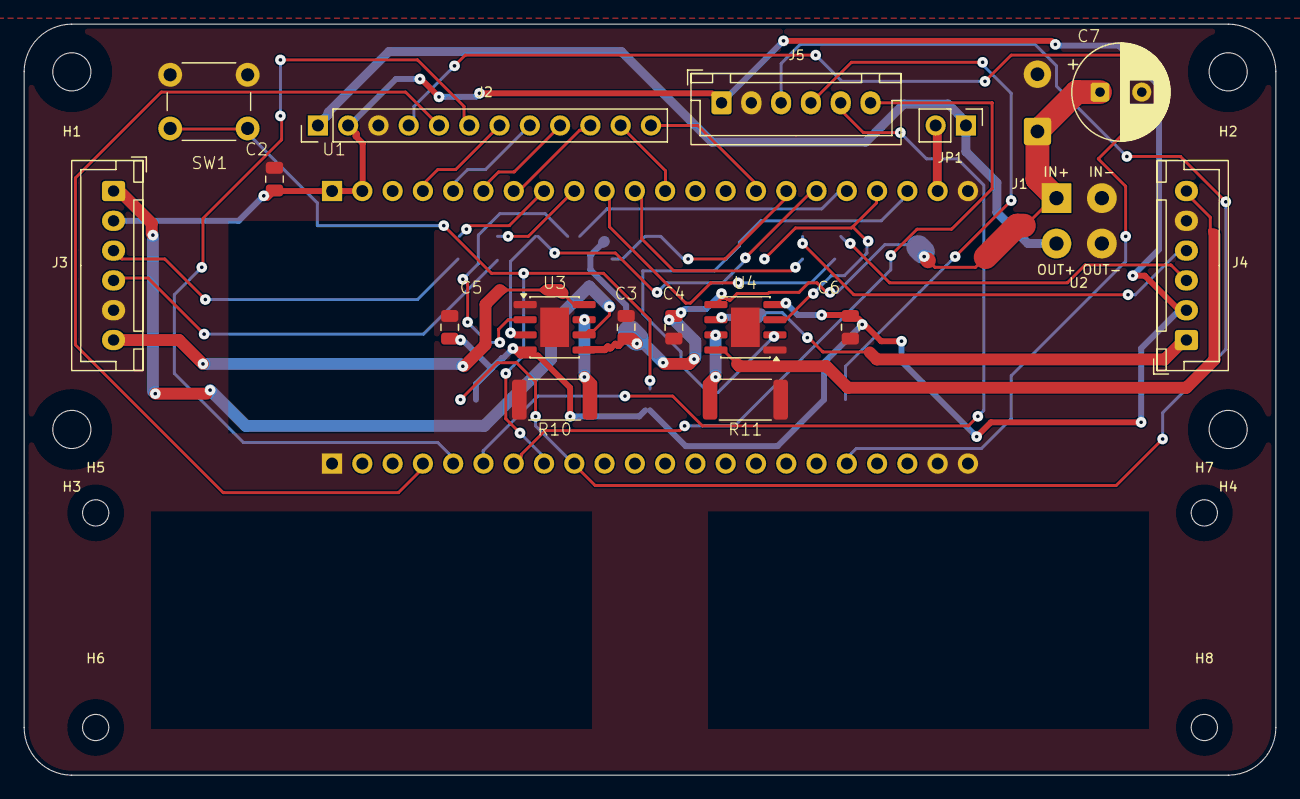
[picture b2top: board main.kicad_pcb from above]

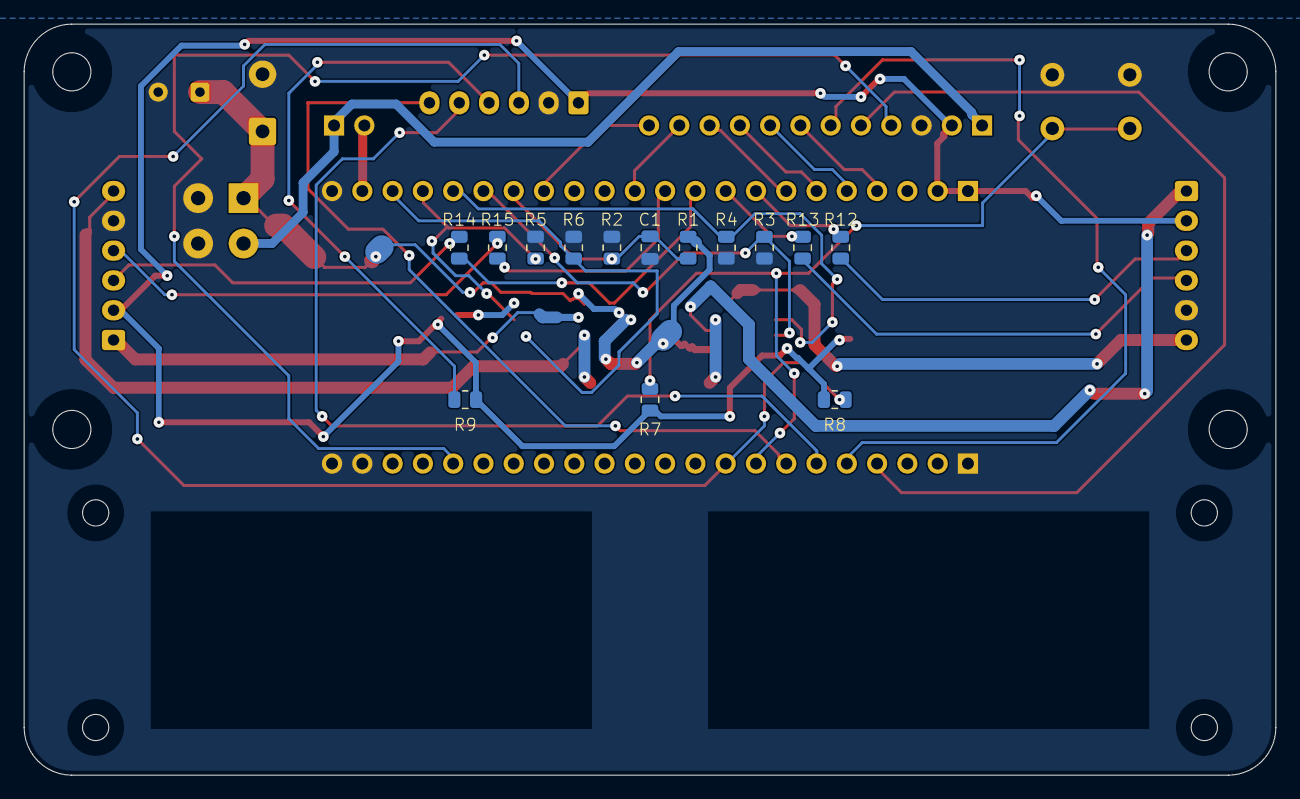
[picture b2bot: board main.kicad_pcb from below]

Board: 2 copper layers, 105.0 x 63.0 mm, 41 parts (14 on the bottom side), 38 nets.

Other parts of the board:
H1, H2, H3, H4: M3 STANDOFF; MountingHole_3.2mm_M3
H5, H6, H7, H8: BRACKET 2.2mm - FASTENER TBD; MountingHole_2.2mm_M2
